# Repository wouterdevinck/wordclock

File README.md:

Wordclock
=========

Instructables: http://www.instructables.com/id/wordclock/

<br />This work is licensed under a <a rel="license" href="http://creativecommons.org/licenses/by-nc-sa/4.0/">Creative Commons Attribution-NonCommercial-ShareAlike 4.0 International License</a>.

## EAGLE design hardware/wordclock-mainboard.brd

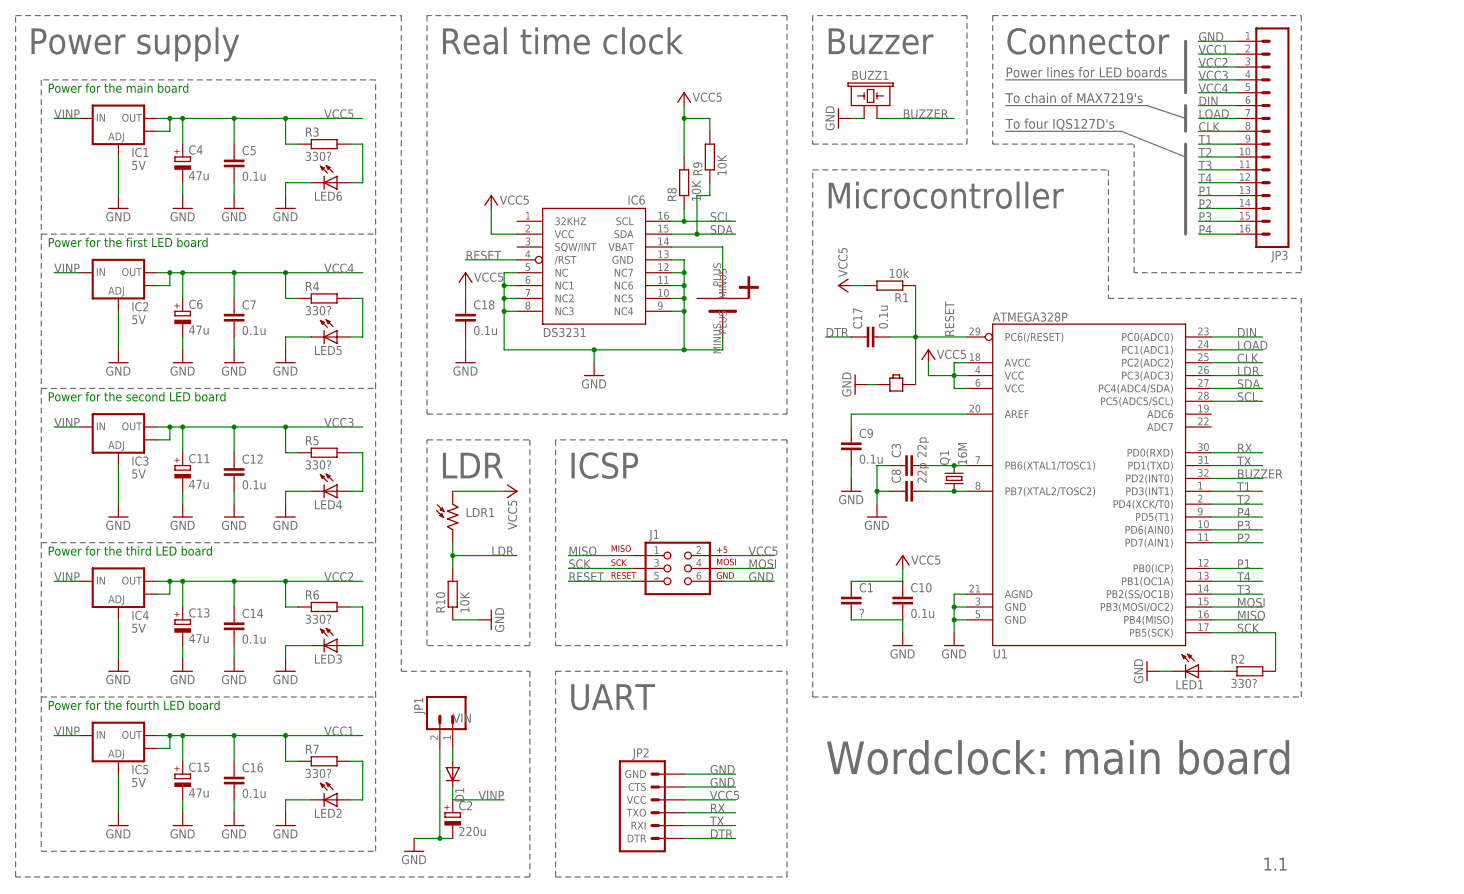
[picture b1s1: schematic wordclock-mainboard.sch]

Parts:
BUZZ1: BUZZERPTH; BUZZER-12MM
C1: ?; C0805
C2: 220u; PANASONIC_D
C3, C8: 22p; C0805
C4, C6, C11, C13, C15: 47u; PANASONIC_D
C5, C7, C9, C10, C12, C14, C16, C17, C18: 0.1u; C0805
D1: DIODE-DO-214AC; DO-214AC
IC1, IC2, IC3, IC4, IC5: 5V; SOT223
IC6: DS3231/SO; SO16W
J1: AVR_SPI_PRG_6PTH; 2X3
JP1: M02PTH; 1X02
JP2: ARDUINO_SERIAL_PROGRAMPTH; 1X06
JP3: M161X16_NO_SILK; 1X16_NO_SILK
LDR1: A1050_09; T0-46-A10XX
LED1, LED2, LED3, LED4, LED5, LED6: LEDCHIPLED_0603; CHIPLED_0603
Q1: 16M; CSM-7X-DU
R1: 10k; R0603
R2, R3, R4, R5, R6, R7: 330?; R0603
R8, R9, R10: 10K; R0603
RESET: BUTTON-SMD-2P; BUTTON_2P_SMD
U1: ATMEGA328P; TQFP32-08
U$1: SMD-CR2032; SMD-BATT

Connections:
BUZZER: BUZZ1.- (2), U1.32 (PD2(INT0))
CLK: JP3.8, U1.25 (PC2(ADC2))
DIN: JP3.6, U1.23 (PC0(ADC0))
DTR: C17.1, JP2.1 (DTR)
GND: BUZZ1.+ (1), C1.2, C2.-, C3.1, C4.-, C5.2, C6.-, C7.2, C8.1, C9.2, C10.2, C11.-, C12.2, C13.-, C14.2, C15.-, C16.2, C18.2, IC1.1 (ADJ), IC2.1 (ADJ), IC3.1 (ADJ), IC4.1 (ADJ), IC5.1 (ADJ), IC6.5 (NC), IC6.6 (NC1), IC6.7 (NC2), IC6.8 (NC3), IC6.9 (NC4), IC6.10 (NC5), IC6.11 (NC6), IC6.12 (NC7), IC6.13 (GND), J1.6, JP1.2, JP2.5 (CTS), JP2.6 (GND), JP3.1, LED1.C, LED2.C, LED3.C, LED4.C, LED5.C, LED6.C, R10.1, RESET.1, U1.3 (GND), U1.5 (GND), U1.21 (AGND), U$1.MINUS
LDR: LDR1.2, R10.2, U1.26 (PC3(ADC3))
LOAD: JP3.7, U1.24 (PC1(ADC1))
MISO: J1.1, U1.16 (PB4(MISO))
MOSI: J1.4, U1.15 (PB3(MOSI/OC2))
unnamed: C3.2, Q1.2, U1.7 (PB6(XTAL1/TOSC1))
unnamed: C8.2, Q1.1, U1.8 (PB7(XTAL2/TOSC2))
unnamed: LED1.A, R2.1
unnamed: LED2.A, R7.2
unnamed: C9.1, U1.20 (AREF)
unnamed: LED3.A, R6.2
unnamed: LED4.A, R5.2
unnamed: LED6.A, R3.2
unnamed: LED5.A, R4.2
unnamed: IC6.14 (VBAT), U$1.PLUS
P1: JP3.13, U1.12 (PB0(ICP))
P2: JP3.14, U1.11 (PD7(AIN1))
P3: JP3.15, U1.10 (PD6(AIN0))
P4: JP3.16, U1.9 (PD5(T1))
RESET: C17.2, IC6.4 (/RST), J1.5, R1.1, RESET.P$2, U1.29 (PC6(/RESET))
RX: JP2.3 (TXO), U1.30 (PD0(RXD))
SCK: J1.3, R2.2, U1.17 (PB5(SCK))
SCL: IC6.16 (SCL), R8.1, U1.28 (PC5(ADC5/SCL))
SDA: IC6.15 (SDA), R9.1, U1.27 (PC4(ADC4/SDA))
T1: JP3.9, U1.1 (PD3(INT1))
T2: JP3.10, U1.2 (PD4(XCK/T0))
T3: JP3.11, U1.14 (PB2(SS/OC1B))
T4: JP3.12, U1.13 (PB1(OC1A))
TX: JP2.2 (RXI), U1.31 (PD1(TXD))
VCC1: C15.+, C16.1, IC5.2 (OUT), IC5.4 (OUT), JP3.2, R7.1
VCC2: C13.+, C14.1, IC4.2 (OUT), IC4.4 (OUT), JP3.3, R6.1
VCC3: C11.+, C12.1, IC3.2 (OUT), IC3.4 (OUT), JP3.4, R5.1
VCC4: C6.+, C7.1, IC2.2 (OUT), IC2.4 (OUT), JP3.5, R4.1
VCC5: C1.1, C4.+, C5.1, C10.1, C18.1, IC1.2 (OUT), IC1.4 (OUT), IC6.2 (VCC), J1.2, JP2.4 (VCC), LDR1.1, R1.2, R3.1, R8.2, R9.2, U1.4 (VCC), U1.6 (VCC), U1.18 (AVCC)
VIN: D1.A, JP1.1
VINP: C2.+, D1.C, IC1.3 (IN), IC2.3 (IN), IC3.3 (IN), IC4.3 (IN), IC5.3 (IN)

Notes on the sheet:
Power supply
Wordclock: main board
1.1
Microcontroller
Power for the main board
ICSP
Power for the first LED board
Power for the second LED board
Power for the third LED board
Power for the fourth LED board
UART
Real time clock
LDR
Buzzer
Connector
Power lines for LED boards
To chain of MAX7219's
To four IQS127D's

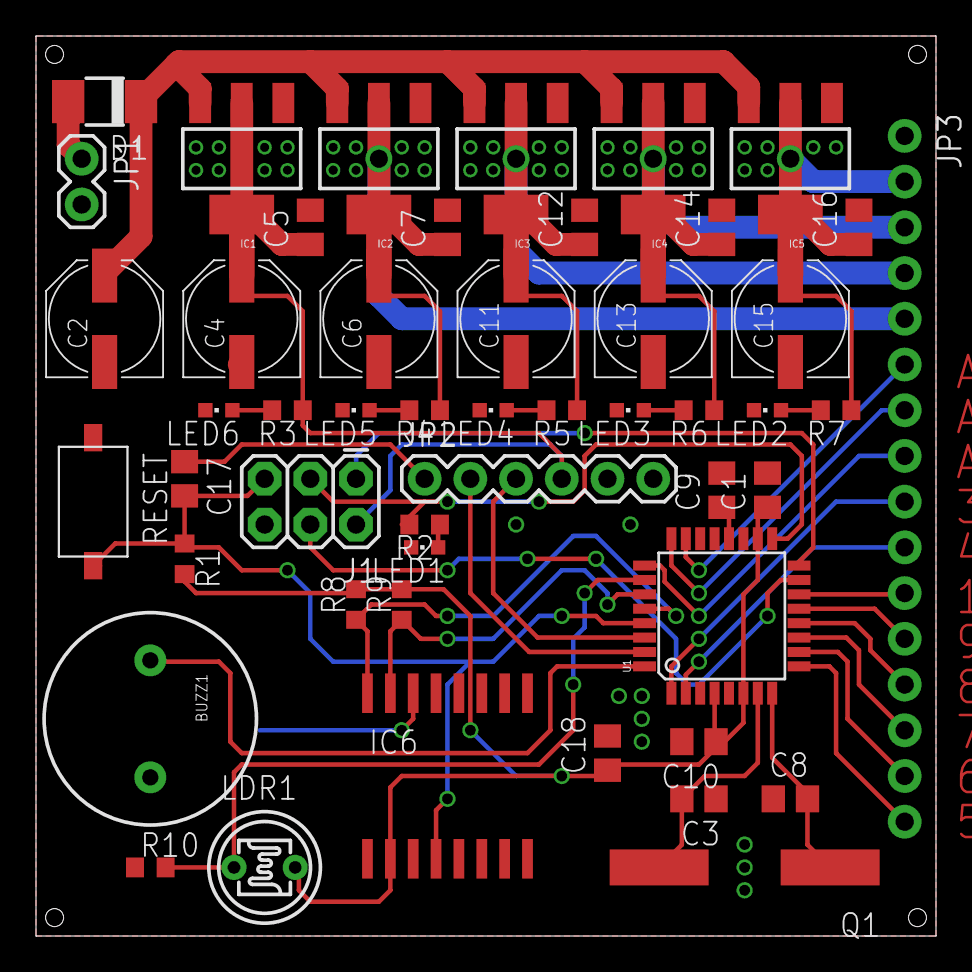
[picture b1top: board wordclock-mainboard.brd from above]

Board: 4 copper layers, 50.0 x 50.0 mm, 51 parts (1 on the bottom side), 40 nets.

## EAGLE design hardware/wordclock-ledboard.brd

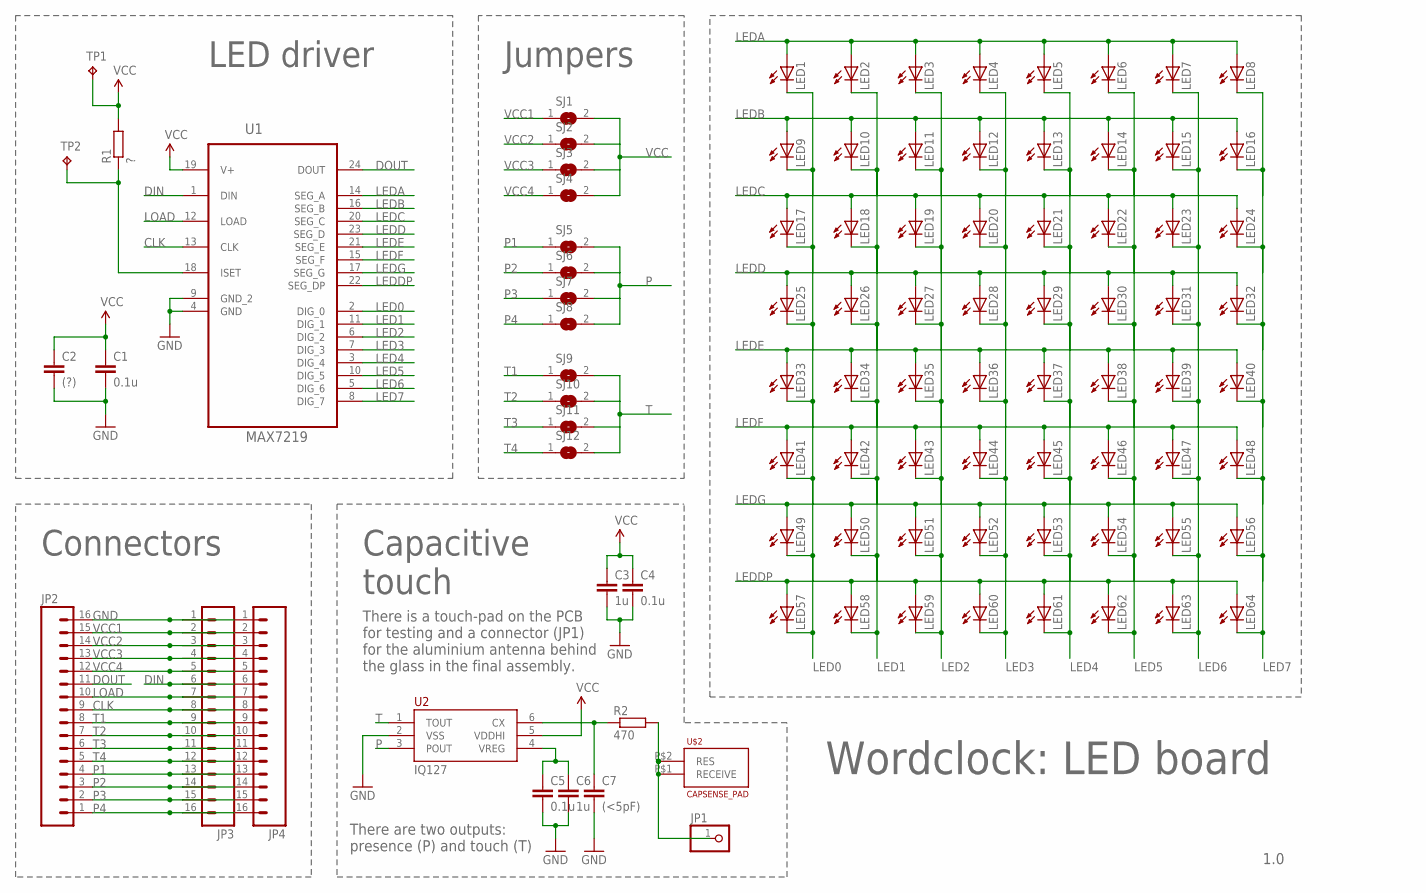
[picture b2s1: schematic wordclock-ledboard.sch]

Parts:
C1, C4, C5: 0.1u; C0805
C2: (?); C0805
C3, C6: 1u; C0805
C7: (<5pF); C0805
JP1: PINHD-1X1; 1X01
JP2, JP3, JP4: M161X16_NO_SILK; 1X16_NO_SILK
LED1, LED2, LED3, LED4, LED5, LED6, LED7, LED8, LED9, LED10, LED11, LED12, LED13, LED14, LED15, LED16, LED17, LED18, LED19, LED20, LED21, LED22, LED23, LED24, LED25, LED26, LED27, LED28, LED29, LED30, LED31, LED32, LED33, LED34, LED35, LED36, LED37, LED38, LED39, LED40, LED41, LED42, LED43, LED44, LED45, LED46, LED47, LED48, LED49, LED50, LED51, LED52, LED53, LED54, LED55, LED56, LED57, LED58, LED59, LED60, LED61, LED62, LED63, LED64: LEDKA-3528ASYC; KA-3528ASYC
R1: ?; R0603
R2: 470; R0603
SJ1, SJ2, SJ3, SJ4, SJ5, SJ6, SJ7, SJ8, SJ9, SJ10, SJ11, SJ12: SJW
TP1, TP2: TPTP20R; TP20R
U1: MAX7219; SOIC127P1032X265-24N
U2: IQ127; TSOT-23-6
U$2: CAPSENSE_PAD

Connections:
C6: C5.1, C6.1, U2.4 (VREG)
CLK: JP2.9, JP3.8, JP4.8, U1.13 (CLK)
DIN: JP3.6, JP4.6, U1.1 (DIN)
DOUT: JP2.11, U1.24 (DOUT)
GND: C1.2, C2.2, C3.2, C4.2, C5.2, C6.2, C7.2, JP2.16, JP3.1, JP4.1, U1.4 (GND), U1.9 (GND_2), U2.2 (VSS)
LED0: LED1.C, LED9.C, LED17.C, LED25.C, LED33.C, LED41.C, LED49.C, LED57.C, U1.2 (DIG_0)
LED1: LED2.C, LED10.C, LED18.C, LED26.C, LED34.C, LED42.C, LED50.C, LED58.C, U1.11 (DIG_1)
LED2: LED3.C, LED11.C, LED19.C, LED27.C, LED35.C, LED43.C, LED51.C, LED59.C, U1.6 (DIG_2)
LED3: LED4.C, LED12.C, LED20.C, LED28.C, LED36.C, LED44.C, LED52.C, LED60.C, U1.7 (DIG_3)
LED4: LED5.C, LED13.C, LED21.C, LED29.C, LED37.C, LED45.C, LED53.C, LED61.C, U1.3 (DIG_4)
LED5: LED6.C, LED14.C, LED22.C, LED30.C, LED38.C, LED46.C, LED54.C, LED62.C, U1.10 (DIG_5)
LED6: LED7.C, LED15.C, LED23.C, LED31.C, LED39.C, LED47.C, LED55.C, LED63.C, U1.5 (DIG_6)
LED7: LED8.C, LED16.C, LED24.C, LED32.C, LED40.C, LED48.C, LED56.C, LED64.C, U1.8 (DIG_7)
LEDA: LED1.A, LED2.A, LED3.A, LED4.A, LED5.A, LED6.A, LED7.A, LED8.A, U1.14 (SEG_A)
LEDB: LED9.A, LED10.A, LED11.A, LED12.A, LED13.A, LED14.A, LED15.A, LED16.A, U1.16 (SEG_B)
LEDC: LED17.A, LED18.A, LED19.A, LED20.A, LED21.A, LED22.A, LED23.A, LED24.A, U1.20 (SEG_C)
LEDD: LED25.A, LED26.A, LED27.A, LED28.A, LED29.A, LED30.A, LED31.A, LED32.A, U1.23 (SEG_D)
LEDDP: LED57.A, LED58.A, LED59.A, LED60.A, LED61.A, LED62.A, LED63.A, LED64.A, U1.22 (SEG_DP)
LEDE: LED33.A, LED34.A, LED35.A, LED36.A, LED37.A, LED38.A, LED39.A, LED40.A, U1.21 (SEG_E)
LEDF: LED41.A, LED42.A, LED43.A, LED44.A, LED45.A, LED46.A, LED47.A, LED48.A, U1.15 (SEG_F)
LEDG: LED49.A, LED50.A, LED51.A, LED52.A, LED53.A, LED54.A, LED55.A, LED56.A, U1.17 (SEG_G)
LOAD: JP2.10, JP3.7, JP4.7, U1.12 (LOAD)
unnamed: JP1.1, R2.2, U$2.P$1 (RECEIVE), U$2.P$2 (RES)
unnamed: R1.1, TP2.TP, U1.18 (ISET)
unnamed: C7.1, R2.1, U2.6 (CX)
P: SJ5.2, SJ6.2, SJ7.2, SJ8.2, U2.3 (POUT)
P1: JP2.4, JP3.13, JP4.13, SJ5.1
P2: JP2.3, JP3.14, JP4.14, SJ6.1
P3: JP2.2, JP3.15, JP4.15, SJ7.1
P4: JP2.1, JP3.16, JP4.16, SJ8.1
T: SJ9.2, SJ10.2, SJ11.2, SJ12.2, U2.1 (TOUT)
T1: JP2.8, JP3.9, JP4.9, SJ9.1
T2: JP2.7, JP3.10, JP4.10, SJ10.1
T3: JP2.6, JP3.11, JP4.11, SJ11.1
T4: JP2.5, JP3.12, JP4.12, SJ12.1
VCC: C1.1, C2.1, C3.1, C4.1, R1.2, SJ1.2, SJ2.2, SJ3.2, SJ4.2, TP1.TP, U1.19 (V+), U2.5 (VDDHI)
VCC1: JP2.15, JP3.2, JP4.2, SJ1.1
VCC2: JP2.14, JP3.3, JP4.3, SJ2.1
VCC3: JP2.13, JP3.4, JP4.4, SJ3.1
VCC4: JP2.12, JP3.5, JP4.5, SJ4.1

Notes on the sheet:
Wordclock: LED board
1.0
LED driver
Jumpers
IQ127
Capacitive touch
Connectors
There is a touch-pad on the PCB for testing and a connector (JP1) for the aluminium antenna behind the glass in the final assembly.
There are two outputs: presence (P) and touch (T)

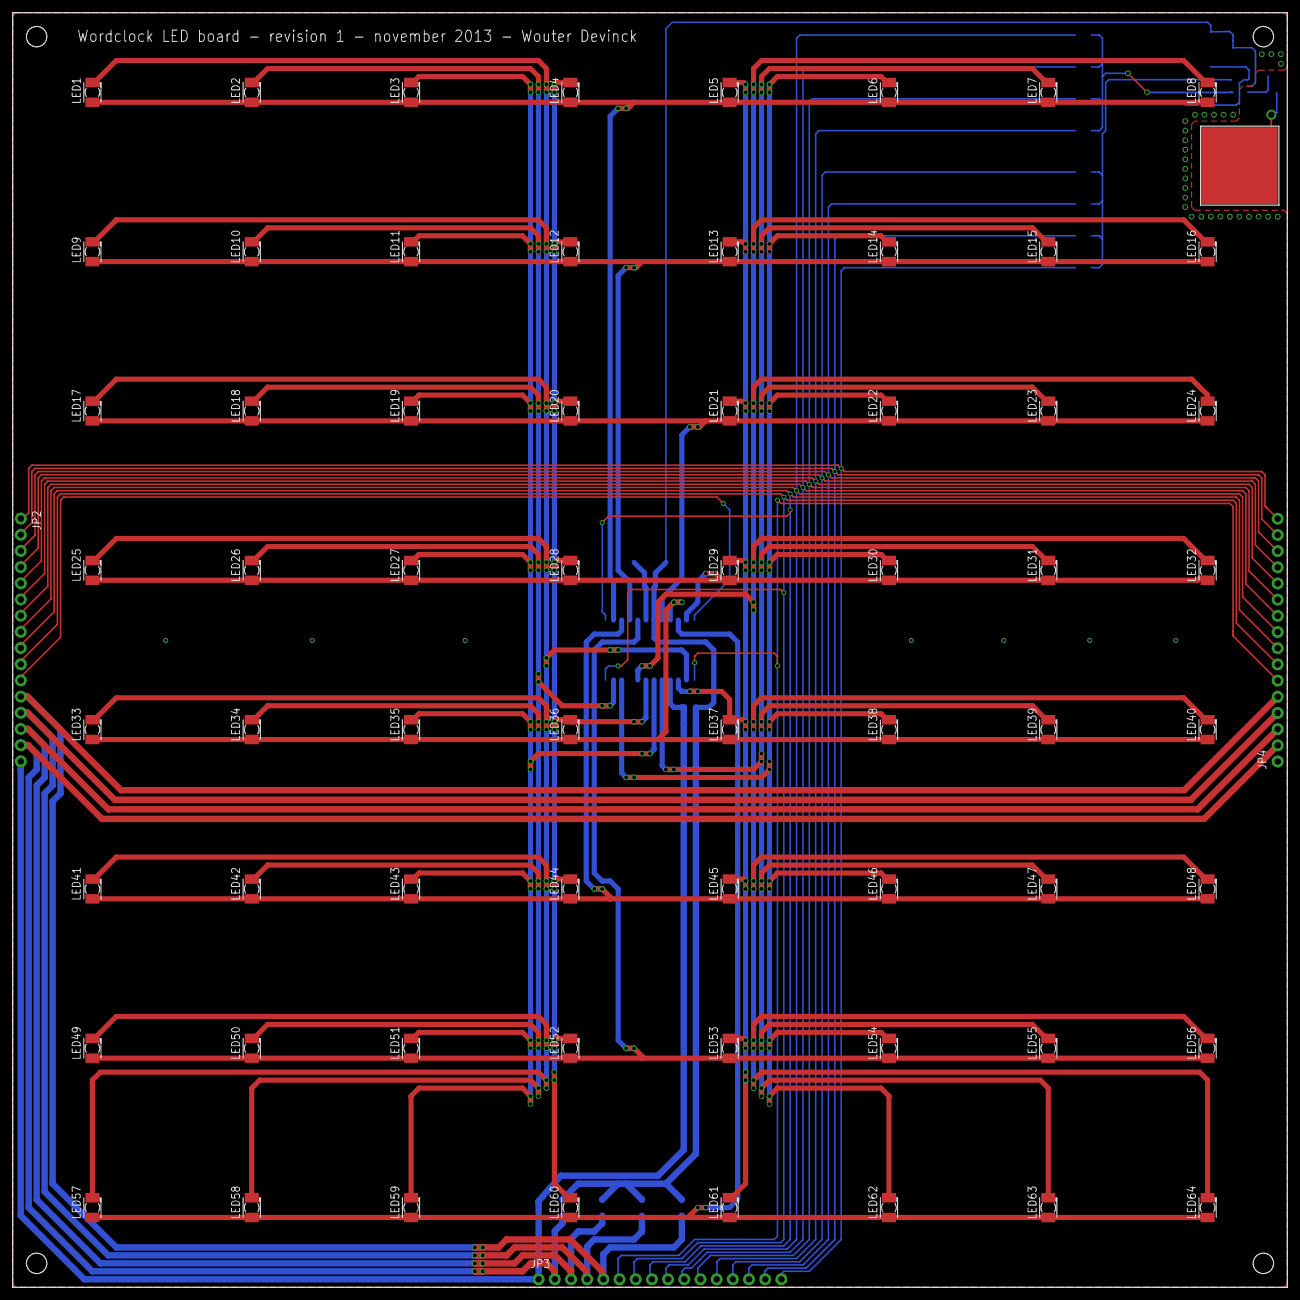
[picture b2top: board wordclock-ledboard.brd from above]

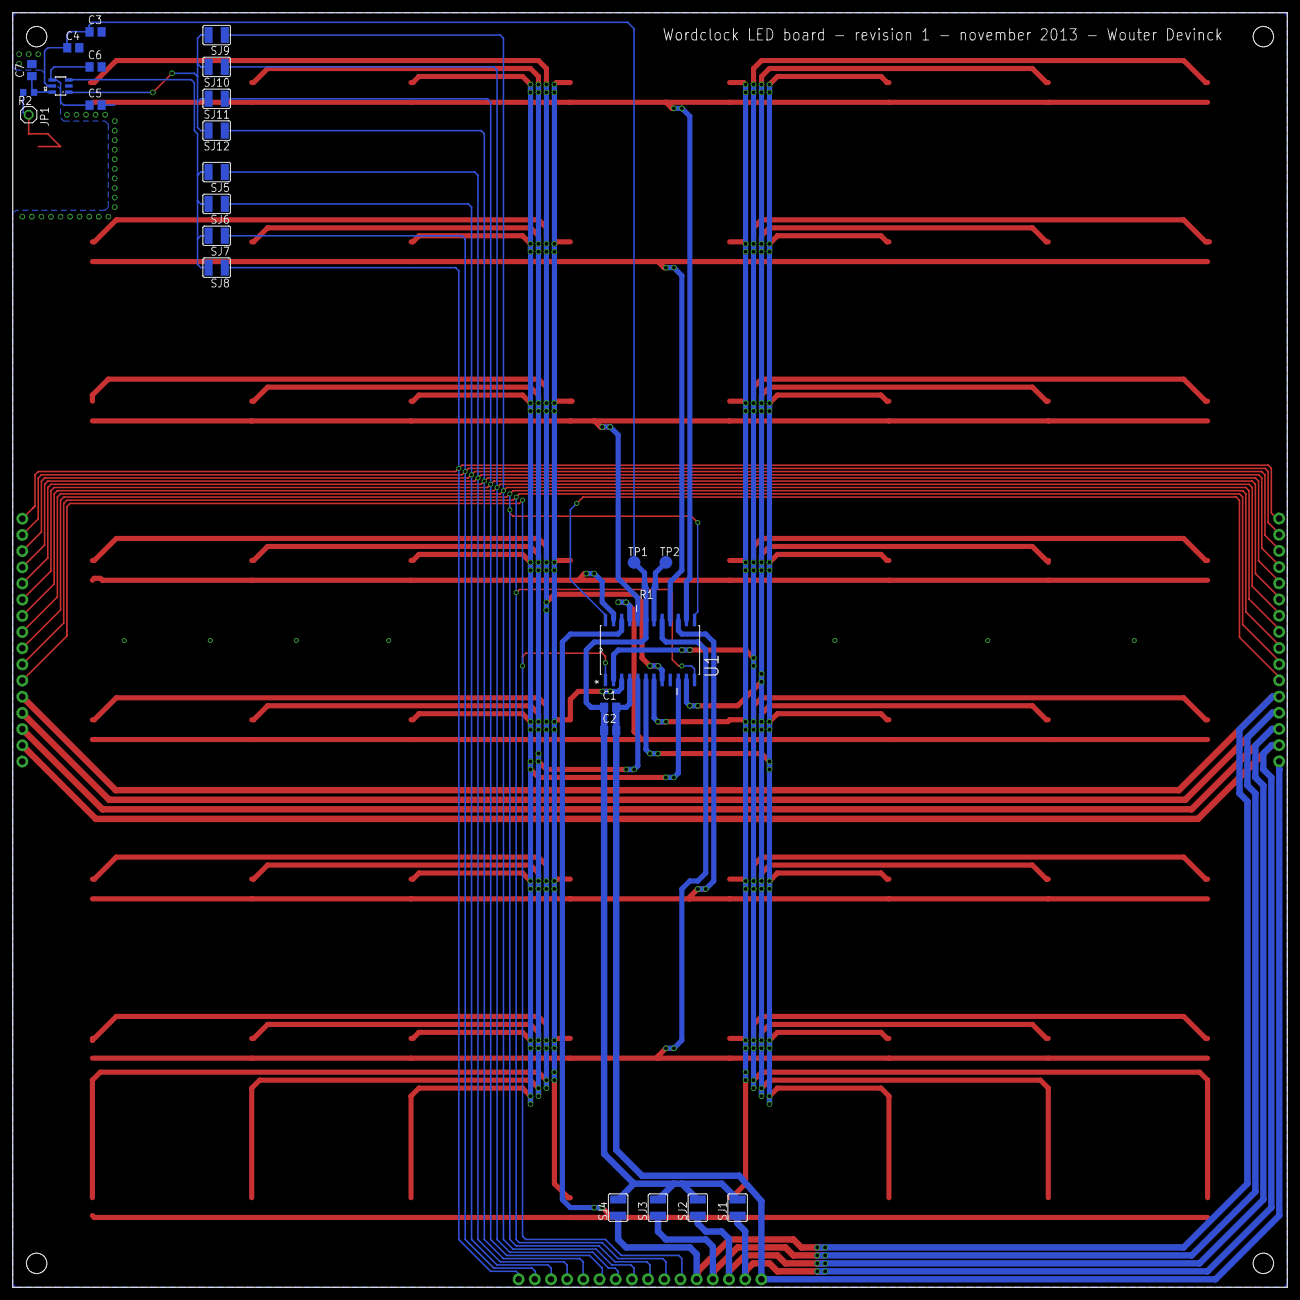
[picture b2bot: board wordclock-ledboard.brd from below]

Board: 4 copper layers, 200.0 x 200.0 mm, 94 parts (26 on the bottom side), 40 nets.

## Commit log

2014-08-10 Readme
2014-08-10 First version of firmware
2014-08-10 Schematics and boards
2014-08-10 Drawings and images
2014-08-11 Faceplate
2014-08-31 Screenshots PCBs
2014-09-03 Gerbers
2014-09-03 Inkskape files

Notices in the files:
parts and their libraries:
SparkFun-Connectors: Licensing: CC v3.0 Share-Alike You are welcome to use this library for commercial purposes.
